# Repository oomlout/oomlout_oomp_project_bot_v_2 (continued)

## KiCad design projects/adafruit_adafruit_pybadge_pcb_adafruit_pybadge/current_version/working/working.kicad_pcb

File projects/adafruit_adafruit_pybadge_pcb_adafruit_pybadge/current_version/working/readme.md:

# adafruit_pybadge_pcb
 
## summary 
* id: adafruit_adafruit_pybadge_pcb_adafruit_pybadge
* user: adafruit
* name: adafruit_pybadge_pcb
* board: adafruit_pybadge
* repo: https://github.com/adafruit/Adafruit-PyBadge-PCB

* src_file_repo_sch: 
* src_file_repo_sch_link: https://github.com/adafruit/Adafruit-PyBadge-PCB/tree/master/
* full details link: https://github.com/oomlout/oomlout_oomp_project_bot_v_2/tree/main/projects/adafruit_adafruit_pybadge_pcb_adafruit_pybadge/current_version/working  

## schematic  
  
[schematic (pdf)](working_schematic.pdf) 

## pcb  

[board (pdf)](working.pdf)  

## working_bom
| Id | Designator | Footprint | Quantity | Designation | Supplier and ref |  | None | 
| --- | --- | --- | --- | --- | --- | --- | --- | 
| 1 | MS1 | FEATHERWING_SMT_NOHOLES | 1 | FEATHERWING_SMTDUALNOHOLES |  |  | [''] | 
| 2 | U4 | ALS-PT26-21C | 1 | ALS-PT21 |  |  | [''] | 
| 3 | C8,C6,C3 | 0805-NO | 3 | 10ÂµF |  |  | [''] | 
| 4 | SJ2 | SOLDERJUMPER_CLOSEDWIRE | 1 |  |  |  | [''] | 
| 5 | U$17,U$15,U$5,U$6 | MOUNTINGHOLE_3.0_PLATEDTHIN | 4 | MOUNTINGHOLE3.0THIN |  |  | [''] | 
| 6 | X1 | JSTPH2 | 1 | JSTPH |  |  | [''] | 
| 7 | C10,C5,C15,C14,C18,C11 | 0805-NO | 6 | 10uF |  |  | [''] | 
| 8 | X2 | 2X05_1.27MM_BOX_POSTS | 1 | 2x5 0.05 SWD" |  |  | [''] | 
| 9 | R14,R15,R3 | 0603-NO | 3 | 10K |  |  | [''] | 
| 10 | FB1 | 0805-NO | 1 | Ferrite |  |  | [''] | 
| 11 | Q1,Q2 | SOT23-R | 2 | DMG3405 |  |  | [''] | 
| 12 | D2,D1 | SOD-323 | 2 | 3.6V |  |  | [''] | 
| 13 | R1,R10,R11 | RESPACK_4X0603 | 3 | 100K |  |  | [''] | 
| 14 | R17,R19 | 0603-NO | 2 | 100K |  |  | [''] | 
| 15 | R7 | 0603-NO | 1 | 2.2K |  |  | [''] | 
| 16 | L0 | CHIPLED_0805_NOOUTLINE | 1 | RED |  |  | [''] | 
| 17 | NEOPIX0,SENSE0 | JSTPH3 | 2 | JST PH 3 |  |  | [''] | 
| 18 | C7,C1,C4,C12,C2,C13,C19 | 0603-NO | 7 | 1uF |  |  | [''] | 
| 19 | R8 | 0603-NO | 1 | 4.7K |  |  | [''] | 
| 20 | IC2 | SOT23-6 | 1 | PAM8301 |  |  | [''] | 
| 21 | U1 | SOIC8_208MIL | 1 | GD25Q16 |  |  | [''] | 
| 22 | SJ1 | SOLDERJUMPER_2WAY_OPEN_NOPASTE | 1 |  |  |  | [''] | 
| 23 | IC4 | LGA16_3X3MM | 1 | LIS3DH |  |  | [''] | 
| 24 | R16 | 0603-NO | 1 | 10 |  |  | [''] | 
| 25 | TP7,TP6,TP8 | TESTPOINT_ROUND_2MM | 3 |  |  |  | [''] | 
| 26 | C16 | _0805MP | 1 | 10ÂµF |  |  | [''] | 
| 27 | IC1 | TSSOP16 | 1 | 74165TSSOP |  |  | [''] | 
| 28 | C17,C9 | 0603-NO | 2 | 0.1uF |  |  | [''] | 
| 29 | U$13 | 53398-0271 | 1 | CON_MOLEX_2P |  |  | [''] | 
| 30 | Q4 | SOT363 | 1 | BSS138 |  |  | [''] | 
| 31 | R6,R5,R2 | 0603-NO | 3 | 1K |  |  | [''] | 
| 32 | U$8 | SPEAKER_OVAL8OHM | 1 |  |  |  | [''] | 
| 33 | U$34,U$35,U$42,U$43 | FIDUCIAL_1MM | 4 | FIDUCIAL_1MM |  |  | [''] | 
| 34 | D4 | SOD-123 | 1 | MBR0540 |  |  | [''] | 
| 35 | CHG0 | CHIPLED_0805_NOOUTLINE | 1 | ORANGE |  |  | [''] | 
| 36 | R12 | 0603-NO | 1 | 47K |  |  | [''] | 
| 37 | SW1 | EVQ-Q2_SMALLER | 1 | SPST_TACT-EVQQ2 |  |  | [''] | 
| 38 | U$32 | PYBADGE_BOT | 1 |  |  |  | [''] | 
| 39 | U$37 | PCBFEAT-REV-040 | 1 |  |  |  | [''] | 
| 40 | X3 | 4UCONN_20329_V2 | 1 | microUSB |  |  | [''] | 
| 41 | U2 | SOT23-5 | 1 | AP2112-3.3 |  |  | [''] | 
| 42 | SW11 | SPDT_SMT_SSSS811101 | 1 |  |  |  | [''] | 
| 43 | SP1 | BUZZER_SMT_7.5MM | 1 | SPEAKER_7.5MM |  |  | [''] | 
| 44 | U3 | SOT23-5 | 1 | MCP73831T-2ACI/OT |  |  | [''] | 
| 45 | I2C0 | JSTPH4 | 1 | JST PH 4 |  |  | [''] | 
| 46 | Q3 | SOT23-WIDE | 1 | BSS138 |  |  | [''] | 
| 47 | R4 | RESPACK_4X0603 | 1 | 10K |  |  | [''] | 
| 48 | U$24 | PQFN64-1 | 1 | ATSAMD51J19 |  |  | [''] | 
| 49 | LED3,LED4,LED1,LED5,LED2 | LED3535 | 5 | WS2812B3535 |  |  | [''] | 
| 50 | B0,RIGHT0,A0,LEFT0,START0,DOWN0,SELECT0,UP0 | 6MM_SMT | 8 |  |  |  | [''] | 
| 51 | U$18 | PYBADGE_TOP | 1 |  |  |  | [''] | 
| 52 | LCD1 | JD-T1800 | 1 | DISP_LCD_JDT1800 |  |  | [''] | 
| 53 | R9 | 0603-NO | 1 | DNP |  |  | [''] | 

## bom_schematic
| Ref | Qnty | Value | Cmp name | Footprint | Description | Vendor | DNP | 
| --- | --- | --- | --- | --- | --- | --- | --- | 
| A0 | 1 | SWITCH_TACT_SMT_6MMSMALL | SWITCH_TACT_SMT_6MMSMALL | working:6MM_SMT |  |  |  | 
| B0 | 1 | SWITCH_TACT_SMT_6MMSMALL | SWITCH_TACT_SMT_6MMSMALL | working:6MM_SMT |  |  |  | 
| C1, C2, C4, C7, C12, C13, C19 | 7 | 1uF | CAP_CERAMIC0603_NO | working:0603-NO |  |  |  | 
| C3, C6, C8 | 3 | 10ÂµF | CAP_CERAMIC0805-NOOUTLINE | working:0805-NO |  |  |  | 
| C5, C10, C11, C14, C15, C18 | 6 | 10uF | CAP_CERAMIC0805-NOOUTLINE | working:0805-NO |  |  |  | 
| C9, C17 | 2 | 0.1uF | CAP_CERAMIC0603_NO | working:0603-NO |  |  |  | 
| C16 | 1 | 10ÂµF | CAP_CERAMIC_0805MP | working:_0805MP |  |  |  | 
| CHG0 | 1 | ORANGE | LED0805_NOOUTLINE | working:CHIPLED_0805_NOOUTLINE |  |  |  | 
| D1, D2 | 2 | 3.6V | DIODE-ZENERSOD323 | working:SOD-323 |  |  |  | 
| D4 | 1 | MBR0540 | DIODE-SCHOTTKYSOD-123 | working:SOD-123 |  |  |  | 
| DOWN0 | 1 | SWITCH_TACT_SMT_6MMSMALL | SWITCH_TACT_SMT_6MMSMALL | working:6MM_SMT |  |  |  | 
| FB1 | 1 | Ferrite | FERRITE-0805NO | working:0805-NO |  |  |  | 
| I2C0 | 1 | STEMMA_I2C_RASMT | STEMMA_I2C_RASMT | working:JSTPH4 |  |  |  | 
| IC1 | 1 | 74165TSSOP | 74165TSSOP | working:TSSOP16 |  |  |  | 
| IC2 | 1 | PAM8301 | PAM8301 | working:SOT23-6 |  |  |  | 
| IC4 | 1 | LIS3DH | ACCEL_LIS3DHTR | working:LGA16_3X3MM |  |  |  | 
| L0 | 1 | RED | LED0805_NOOUTLINE | working:CHIPLED_0805_NOOUTLINE |  |  |  | 
| LCD1 | 1 | DISP_LCD_JDT1800 | DISP_LCD_JDT1800 | working:JD-T1800 |  |  |  | 
| LED1, LED2, LED3, LED4, LED5 | 5 | WS2812B3535 | WS2812B3535 | working:LED3535 |  |  |  | 
| LEFT0 | 1 | SWITCH_TACT_SMT_6MMSMALL | SWITCH_TACT_SMT_6MMSMALL | working:6MM_SMT |  |  |  | 
| MS1 | 1 | FEATHERWING_SMTDUALNOHOLES | FEATHERWING_SMTDUALNOHOLES | working:FEATHERWING_SMT_NOHOLES |  |  |  | 
| NEOPIX0 | 1 | JST PH 3 | CON_JST_PH_3PIN | working:JSTPH3 |  |  |  | 
| Q1, Q2 | 2 | DMG3405 | MOSFET-P | working:SOT23-R |  |  |  | 
| Q3 | 1 | BSS138 | MOSFET-NWIDE | working:SOT23-WIDE |  |  |  | 
| Q4 | 1 | BSS138 | MOSFET-N_DUAL | working:SOT363 |  |  |  | 
| R1, R10, R11 | 3 | 100K | RESISTOR_4PACK | working:RESPACK_4X0603 |  |  |  | 
| R2, R5, R6 | 3 | 1K | RESISTOR_0603_NOOUT | working:0603-NO |  |  |  | 
| R3, R14, R15 | 3 | 10K | RESISTOR_0603_NOOUT | working:0603-NO |  |  |  | 
| R4 | 1 | 10K | RESISTOR_4PACK | working:RESPACK_4X0603 |  |  |  | 
| R7 | 1 | 2.2K | RESISTOR_0603_NOOUT | working:0603-NO |  |  |  | 
| R8 | 1 | 4.7K | RESISTOR_0603_NOOUT | working:0603-NO |  |  |  | 
| R9 | 1 | DNP | RESISTOR_0603_NOOUT | working:0603-NO |  |  |  | 
| R12 | 1 | 47K | RESISTOR_0603_NOOUT | working:0603-NO |  |  |  | 
| R16 | 1 | 10 | RESISTOR_0603_NOOUT | working:0603-NO |  |  |  | 
| R17, R19 | 2 | 100K | RESISTOR_0603_NOOUT | working:0603-NO |  |  |  | 
| RIGHT0 | 1 | SWITCH_TACT_SMT_6MMSMALL | SWITCH_TACT_SMT_6MMSMALL | working:6MM_SMT |  |  |  | 
| SELECT0 | 1 | SWITCH_TACT_SMT_6MMSMALL | SWITCH_TACT_SMT_6MMSMALL | working:6MM_SMT |  |  |  | 
| SENSE0 | 1 | JST PH 3 | CON_JST_PH_3PIN | working:JSTPH3 |  |  |  | 
| SJ1 | 1 | SOLDERJUMPER_2WAY | SOLDERJUMPER_2WAY | working:SOLDERJUMPER_2WAY_OPEN_NOPASTE |  |  |  | 
| SJ2 | 1 | SOLDERJUMPERCLOSED | SOLDERJUMPERCLOSED | working:SOLDERJUMPER_CLOSEDWIRE |  |  |  | 
| SP1 | 1 | SPEAKER_7.5MM | SPEAKER_7.5MM | working:BUZZER_SMT_7.5MM |  |  |  | 
| START0 | 1 | SWITCH_TACT_SMT_6MMSMALL | SWITCH_TACT_SMT_6MMSMALL | working:6MM_SMT |  |  |  | 
| SW1 | 1 | SPST_TACT-EVQQ2 | SWITCH_TACT_SMT_EVQQ2_SMALL | working:EVQ-Q2_SMALLER |  |  |  | 
| SW11 | 1 | SWITCH_SPDT | SWITCH_SPDT | working:SPDT_SMT_SSSS811101 |  |  |  | 
| TP6, TP7, TP8 | 3 | TESTPOINTROUND2MM | TESTPOINTROUND2MM | working:TESTPOINT_ROUND_2MM |  |  |  | 
| U1 | 1 | GD25Q16 | SPIFLASH_8PIN208MIL | working:SOIC8_208MIL |  |  |  | 
| U2 | 1 | AP2112-3.3 | VREG_SOT23-5 | working:SOT23-5 |  |  |  | 
| U3 | 1 | MCP73831T-2ACI/OT | MCP73831/2 | working:SOT23-5 |  |  |  | 
| U4 | 1 | ALS-PT21 | PHOTOTRANSISTOR_PT26-21C | working:ALS-PT26-21C |  |  |  | 
| U$5, U$6, U$15, U$17 | 4 | MOUNTINGHOLE3.0THIN | MOUNTINGHOLE3.0THIN | working:MOUNTINGHOLE_3.0_PLATEDTHIN |  |  |  | 
| U$13 | 1 | CON_MOLEX_2P | CON_MOLEX_2P | working:53398-0271 |  |  |  | 
| U$24 | 1 | ATSAMD51J | ATSAMD51J | working:PQFN64-1 |  |  |  | 
| U$34, U$35, U$42, U$43 | 4 | FIDUCIAL_1MM | FIDUCIAL_1MM | working:FIDUCIAL_1MM |  |  |  | 
| UP0 | 1 | SWITCH_TACT_SMT_6MMSMALL | SWITCH_TACT_SMT_6MMSMALL | working:6MM_SMT |  |  |  | 
| X1 | 1 | JSTPH | CON_JST_PH_2PIN | working:JSTPH2 |  |  |  | 
| X2 | 1 | 2x5 0.05" SWD | JTAG-CORTEXBOXPOSTS | working:2X05_1.27MM_BOX_POSTS |  |  |  | 
| X3 | 1 | microUSB | USB_MICRO_20329_V2 | working:4UCONN_20329_V2 |  |  |  | 

## mounting_holes
| x | y | package | value | ref | size | 
| --- | --- | --- | --- | --- | --- | 
| 0.0 | 46.36 | MOUNTINGHOLE_3.0_PLATEDTHIN | MOUNTINGHOLE3.0THIN | U$5 | m3 | 
| 78.1 | 46.36 | MOUNTINGHOLE_3.0_PLATEDTHIN | MOUNTINGHOLE3.0THIN | U$6 | m3 | 
| 0.0 | 0.0 | MOUNTINGHOLE_3.0_PLATEDTHIN | MOUNTINGHOLE3.0THIN | U$15 | m3 | 
| 78.1 | 0.0 | MOUNTINGHOLE_3.0_PLATEDTHIN | MOUNTINGHOLE3.0THIN | U$17 | m3 |

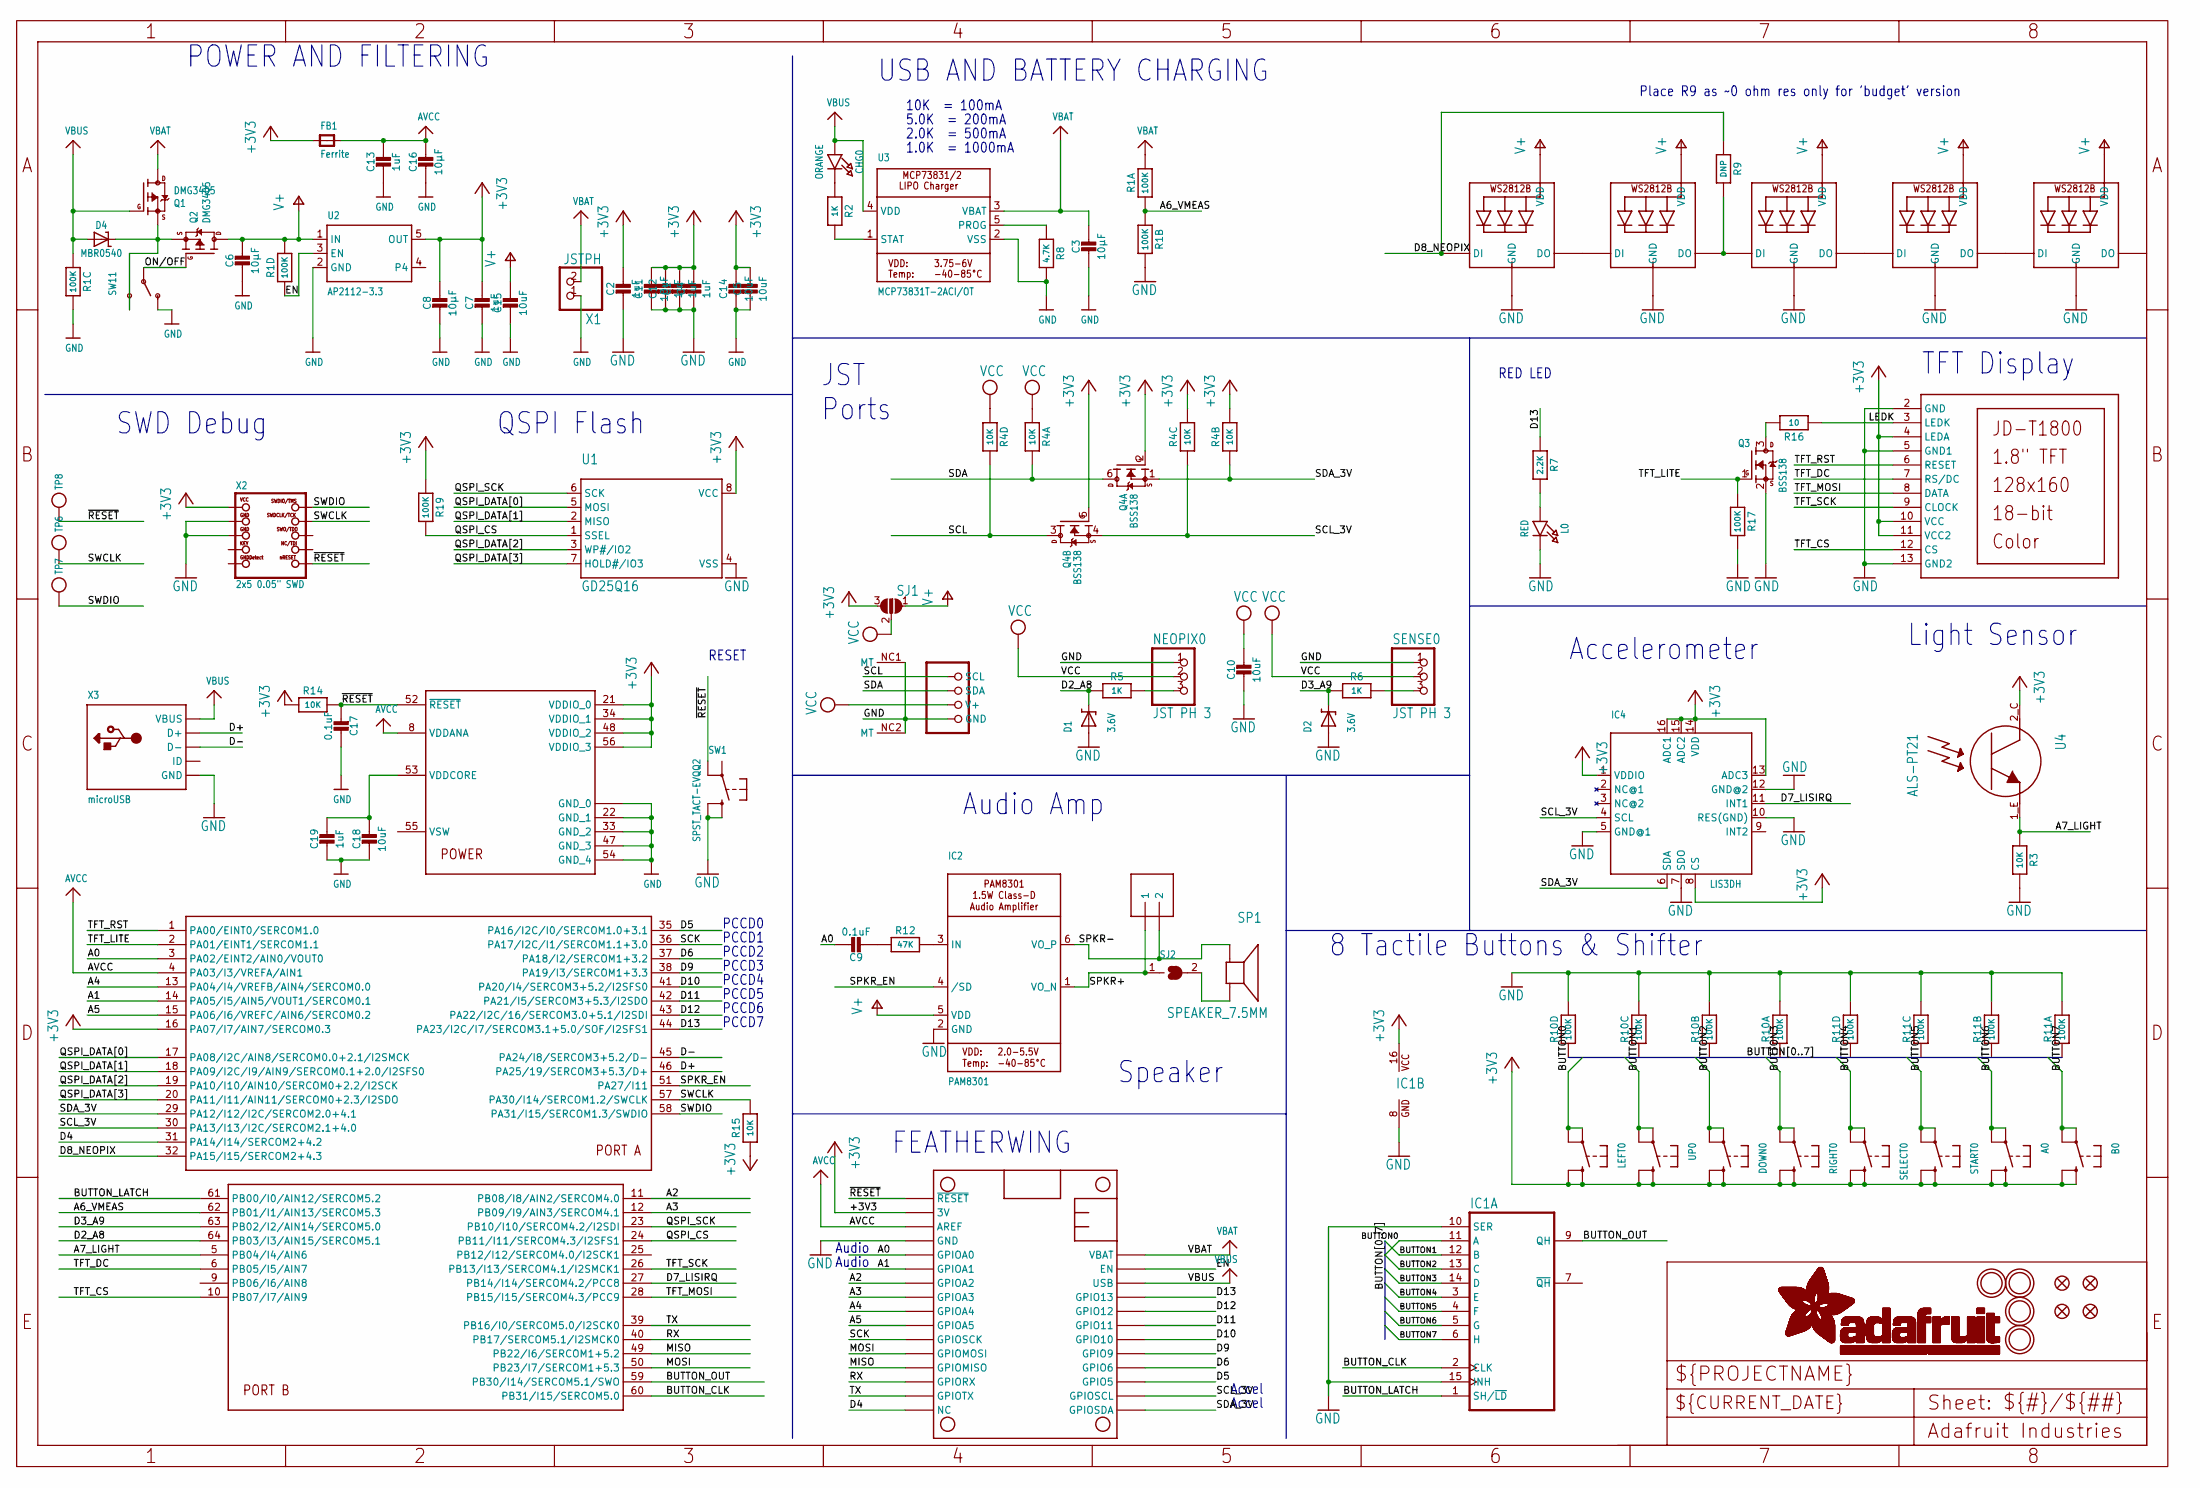
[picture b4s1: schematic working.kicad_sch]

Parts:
A0: SWITCH_TACT_SMT_6MMSMALL; 6MM_SMT
B0: SWITCH_TACT_SMT_6MMSMALL; 6MM_SMT
C1, C2, C4, C7, C12, C13, C19: 1uF; 0603-NO
C3, C6, C8: 10µF; 0805-NO
C5, C10, C11, C14, C15, C18: 10uF; 0805-NO
C9, C17: 0.1uF; 0603-NO
C16: 10µF; _0805MP
CHG0: ORANGE; CHIPLED_0805_NOOUTLINE
D1, D2: 3.6V; SOD-323
D4: MBR0540; SOD-123
DOWN0: SWITCH_TACT_SMT_6MMSMALL; 6MM_SMT
FB1: Ferrite; 0805-NO
I2C0: STEMMA_I2C_RASMT; JSTPH4
IC1: 74165TSSOP; TSSOP16
IC2: PAM8301; SOT23-6
IC4: LIS3DH; LGA16_3X3MM
L0: RED; CHIPLED_0805_NOOUTLINE
LCD1: DISP_LCD_JDT1800; JD-T1800
LED1, LED2, LED3, LED4, LED5: WS2812B3535; LED3535
LEFT0: SWITCH_TACT_SMT_6MMSMALL; 6MM_SMT
MS1: FEATHERWING_SMTDUALNOHOLES; FEATHERWING_SMT_NOHOLES
NEOPIX0: JST PH 3; JSTPH3
Q1, Q2: DMG3405; SOT23-R
Q3: BSS138; SOT23-WIDE
Q4: BSS138; SOT363
R1, R10, R11: 100K; RESPACK_4X0603
R2, R5, R6: 1K; 0603-NO
R3, R14, R15: 10K; 0603-NO
R4: 10K; RESPACK_4X0603
R7: 2.2K; 0603-NO
R8: 4.7K; 0603-NO
R9: DNP; 0603-NO
R12: 47K; 0603-NO
R16: 10; 0603-NO
R17, R19: 100K; 0603-NO
RIGHT0: SWITCH_TACT_SMT_6MMSMALL; 6MM_SMT
SELECT0: SWITCH_TACT_SMT_6MMSMALL; 6MM_SMT
SENSE0: JST PH 3; JSTPH3
SJ1: SOLDERJUMPER_2WAY; SOLDERJUMPER_2WAY_OPEN_NOPASTE
SJ2: SOLDERJUMPERCLOSED; SOLDERJUMPER_CLOSEDWIRE
SP1: SPEAKER_7.5MM; BUZZER_SMT_7.5MM
START0: SWITCH_TACT_SMT_6MMSMALL; 6MM_SMT
SW1: SPST_TACT-EVQQ2; EVQ-Q2_SMALLER
SW11: SWITCH_SPDT; SPDT_SMT_SSSS811101
TP6, TP7, TP8: TESTPOINTROUND2MM; TESTPOINT_ROUND_2MM
U1: GD25Q16; SOIC8_208MIL
U2: AP2112-3.3; SOT23-5
U3: MCP73831T-2ACI/OT; SOT23-5
U4: ALS-PT21; ALS-PT26-21C
U$5, U$6, U$15, U$17: MOUNTINGHOLE3.0THIN; MOUNTINGHOLE_3.0_PLATEDTHIN
U$13: CON_MOLEX_2P; 53398-0271
U$24: ATSAMD51J; PQFN64-1
U$34, U$35, U$42, U$43: FIDUCIAL_1MM
UP0: SWITCH_TACT_SMT_6MMSMALL; 6MM_SMT
X1: JSTPH; JSTPH2
X2: 2x5 0.05" SWD; 2X05_1.27MM_BOX_POSTS
X3: microUSB; 4UCONN_20329_V2

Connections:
+3V3: A0.B (S), A0.B' (S1), B0.B (S), B0.B' (S1), C1.1, C2.1, C4.1, C5.1, C7.1, C8.1, C11.1, C12.1, C14.1, DOWN0.B (S), DOWN0.B' (S1), FB1.1, IC1.16 (VCC), IC4.1 (VDDIO), IC4.8 (CS), IC4.13 (ADC3), IC4.14 (VDD), IC4.15 (ADC2), IC4.16 (ADC1), LCD1.4 (LEDA), LCD1.10 (VCC), LCD1.11 (VCC2), LEFT0.B (S), LEFT0.B' (S1), MS1.2 (3V), MS1.2B (3V), Q4.2 (G), Q4.5 (G), R4.2 (1), R4.3 (1), R14.1, R15.1, R19.1, RIGHT0.B (S), RIGHT0.B' (S1), SELECT0.B (S), SELECT0.B' (S1), SJ1.3, START0.B (S), START0.B' (S1), U1.8 (VCC), U2.5 (OUT), U4.2_C (C), U$24.16 (PA07/I7/AIN7/SERCOM0.3), U$24.21 (VDDIO_0), U$24.34 (VDDIO_1), U$24.48 (VDDIO_2), U$24.56 (VDDIO_3), UP0.B (S), UP0.B' (S1), X2.1 (VCC)
A0: C9.1, MS1.5 (GPIOA0), MS1.5B (GPIOA0), U$24.3 (PA02/EINT2/AIN0/VOUT0)
A1: MS1.6 (GPIOA1), MS1.6B (GPIOA1), U$24.14 (PA05/I5/AIN5/VOUT1/SERCOM0.1)
A2: MS1.7 (GPIOA2), MS1.7B (GPIOA2), U$24.11 (PB08/I8/AIN2/SERCOM4.0)
A3: MS1.8 (GPIOA3), MS1.8B (GPIOA3), U$24.12 (PB09/I9/AIN3/SERCOM4.1)
A4: MS1.9 (GPIOA4), MS1.9B (GPIOA4), U$24.13 (PA04/I4/VREFB/AIN4/SERCOM0.0)
A5: MS1.10 (GPIOA5), MS1.10B (GPIOA5), U$24.15 (PA06/I6/VREFC/AIN6/SERCOM0.2)
A6_VMEAS: R1.1, R1.2 (1), U$24.62 (PB01/I1/AIN13/SERCOM5.3)
A7_LIGHT: R3.2, U4.1_E (E), U$24.5 (PB04/I4/AIN6)
AVCC: C13.1, C16.1, FB1.2, MS1.3 (AREF), MS1.3B (AREF), U$24.4 (PA03/I3/VREFA/AIN1), U$24.8 (VDDANA)
BUTTON0: IC1.11 (A), LEFT0.A, LEFT0.A' (P1), R10.4 (1)
BUTTON1: IC1.12 (B), R10.3 (1), UP0.A, UP0.A' (P1)
BUTTON2: DOWN0.A, DOWN0.A' (P1), IC1.13 (C), R10.2 (1)
BUTTON3: IC1.14 (D), R10.1, RIGHT0.A, RIGHT0.A' (P1)
BUTTON4: IC1.3 (E), R11.4 (1), SELECT0.A, SELECT0.A' (P1)
BUTTON5: IC1.4 (F), R11.3 (1), START0.A, START0.A' (P1)
BUTTON6: A0.A, A0.A' (P1), IC1.5 (G), R11.2 (1)
BUTTON7: B0.A, B0.A' (P1), IC1.6 (H), R11.1
BUTTON_CLK: IC1.2 (CLK), U$24.60 (PB31/I15/SERCOM5.0)
BUTTON_LATCH: IC1.1 (SH/~LD), U$24.61 (PB00/I0/AIN12/SERCOM5.2)
BUTTON_OUT: IC1.9 (QH), U$24.59 (PB30/I14/SERCOM5.1/SWO)
CHG_LED: R2.2, U3.1 (STAT)
CHG_RATE: R8.1, U3.5 (PROG)
D2_: NEOPIX0.3, R5.1
D2_A8: D1.C, R5.2, U$24.64 (PB03/I3/AIN15/SERCOM5.1)
D3_: R6.1, SENSE0.3
D3_A9: D2.C, R6.2, U$24.63 (PB02/I2/AIN14/SERCOM5.0)
D4: MS1.16 (NC), MS1.16B (NC), U$24.31 (PA14/I14/SERCOM2+4.2)
D5: MS1.19 (GPIO5), MS1.19B (GPIO5), U$24.35 (PA16/I2C/I0/SERCOM1.0+3.1)
D6: MS1.20 (GPIO6), MS1.20B (GPIO6), U$24.37 (PA18/I2/SERCOM1+3.2)
D7_LISIRQ: IC4.11 (INT1), U$24.27 (PB14/I14/SERCOM4.2/PCC8)
D8_NEOPIX: LED1.1 (DI), R9.1, U$24.32 (PA15/I15/SERCOM2+4.3)
D9: MS1.21 (GPIO9), MS1.21B (GPIO9), U$24.38 (PA19/I3/SERCOM1+3.3)
D10: MS1.22 (GPIO10), MS1.22B (GPIO10), U$24.41 (PA20/I4/SERCOM3+5.2/I2SFS0)
D11: MS1.23 (GPIO11), MS1.23B (GPIO11), U$24.42 (PA21/I5/SERCOM3+5.3/I2SDO)
D12: MS1.24 (GPIO12), MS1.24B (GPIO12), U$24.43 (PA22/I2C/16/SERCOM3.0+5.1/I2SDI)
D13: MS1.25 (GPIO13), MS1.25B (GPIO13), R7.1, U$24.44 (PA23/I2C/I7/SERCOM3.1+5.0/SOF/I2SFS1)
D+: U$24.46 (PA25/19/SERCOM3+5.3/D+), X3.D+
D-: U$24.45 (PA24/I8/SERCOM3+5.2/D-), X3.D-
EN: MS1.27 (EN), MS1.27B (EN), R1.4 (1), U2.3 (EN)
GND: C1.2, C2.2, C3.2, C4.2, C5.2, C6.2, C7.2, C8.2, C10.2, C11.2, C12.2, C13.2, C14.2, C15.2, C16.2, C17.1, C18.2, C19.2, D1.A, D2.A, I2C0.1 (GND), I2C0.NC1 (MT), I2C0.NC2 (MT), IC1.8 (GND), IC1.10 (SER), IC1.15 (INH), IC2.2 (GND), IC4.5 (GND@1), IC4.7 (SDO), IC4.10 (RES(GND)), IC4.12 (GND@2), L0.C, LCD1.2 (GND), LCD1.5 (GND1), LCD1.13 (GND2), LED1.4 (GND), LED2.4 (GND), LED3.4 (GND), LED4.4 (GND), LED5.4 (GND), MS1.4 (GND), MS1.4B (GND), NEOPIX0.1, Q3.2 (S), R1.6 (2), R1.7 (2), R3.1, R8.2, R10.5 (2), R10.6 (2), R10.7 (2), R10.8 (2), R11.5 (2), R11.6 (2), R11.7 (2), R11.8 (2), R17.2, SENSE0.1, SW1.B (S), SW1.B' (S1), SW11.A (O), U1.4 (VSS), U2.2 (GND), U3.2 (VSS), U$24.7 (GND_0), U$24.22 (GND_1), U$24.33 (GND_2), U$24.47 (GND_3), U$24.54 (GND_4), U$24.EXP (GND_0), X1.1, X2.3 (GND@1), X2.5 (GND@2), X3.BASE@1 (GND), X3.BASE@2 (GND), X3.GND, X3.SPRT@1 (GND), X3.SPRT@2 (GND), X3.SPRT@3 (GND), X3.SPRT@4 (GND)
LEDK: LCD1.3 (LEDK), R16.1
MISO: MS1.13 (GPIOMISO), MS1.13B (GPIOMISO), U$24.49 (PB22/I6/SERCOM1+5.2)
MOSI: MS1.12 (GPIOMOSI), MS1.12B (GPIOMOSI), U$24.50 (PB23/I7/SERCOM1+5.3)
unnamed: CHG0.C, R2.1
unnamed: L0.A, R7.2
unnamed: LED1.3 (DO), LED2.1 (DI)
unnamed: LED2.3 (DO), LED3.1 (DI), R9.2
unnamed: LED3.3 (DO), LED4.1 (DI)
unnamed: Q3.3 (D), R16.2
unnamed: LED4.3 (DO), LED5.1 (DI)
unnamed: D4.C, Q1.2 (S), Q2.2 (S), SW11.C (S)
unnamed: C9.2, R12.1
unnamed: IC2.3 (IN), R12.2
unnamed: SJ2.2, SP1.-
ON/OFF: Q2.1 (G), SW11.B
QSPI_CS: R19.2, U1.1 (SSEL), U$24.24 (PB11/I11/SERCOM4.3/I2SFS1)
QSPI_DATA[0]: U1.5 (MOSI), U$24.17 (PA08/I2C/AIN8/SERCOM0.0+2.1/I2SMCK)
QSPI_DATA[1]: U1.2 (MISO), U$24.18 (PA09/I2C/I9/AIN9/SERCOM0.1+2.0/I2SFS0)
QSPI_DATA[2]: U1.3 (WP#/IO2), U$24.19 (PA10/I10/AIN10/SERCOM0+2.2/I2SCK)
QSPI_DATA[3]: U1.7 (HOLD#/IO3), U$24.20 (PA11/I11/AIN11/SERCOM0+2.3/I2SDO)
QSPI_SCK: U1.6 (SCK), U$24.23 (PB10/I10/SERCOM4.2/I2SDI)
RX: MS1.14 (GPIORX), MS1.14B (GPIORX), U$24.40 (PB17/SERCOM5.1/I2SMCK0)
SCK: MS1.11 (GPIOSCK), MS1.11B (GPIOSCK), U$24.36 (PA17/I2C/I1/SERCOM1.1+3.0)
SCL: I2C0.4 (SCL), Q4.3 (D), R4.5 (2)
SCL_3V: IC4.4 (SCL), MS1.18 (GPIOSCL), MS1.18B (GPIOSCL), Q4.4 (S), R4.6 (2), U$24.30 (PA13/I13/I2C/SERCOM2.1+4.0)
SDA: I2C0.3 (SDA), Q4.6 (D), R4.8 (2)
SDA_3V: IC4.6 (SDA), MS1.17 (GPIOSDA), MS1.17B (GPIOSDA), Q4.1 (S), R4.7 (2), U$24.29 (PA12/I12/I2C/SERCOM2.0+4.1)
SPKR+: IC2.1 (VO_N), SJ2.1, U$13.1
SPKR-: IC2.6 (VO_P), SP1.+, U$13.2
SPKR_EN: IC2.4 (/SD), U$24.51 (PA27/I11)
SWCLK: R15.2, TP6.P$1, U$24.57 (PA30/I14/SERCOM1.2/SWCLK), X2.4 (SWDCLK)
SWDIO: TP7.P$1, U$24.58 (PA31/I15/SERCOM1.3/SWDIO), X2.2 (SWDIO)
TFT_CS: LCD1.12 (CS), U$24.10 (PB07/I7/AIN9)
TFT_DC: LCD1.7 (RS/DC), U$24.6 (PB05/I5/AIN7)
TFT_LITE: Q3.1 (G), R17.1, U$24.2 (PA01/EINT1/SERCOM1.1)
TFT_MOSI: LCD1.8 (DATA), U$24.28 (PB15/I15/SERCOM4.3/PCC9)
TFT_RST: LCD1.6 (RESET), U$24.1 (PA00/EINT0/SERCOM1.0)
TFT_SCK: LCD1.9 (CLOCK), U$24.26 (PB13/I13/SERCOM4.1/I2SMCK1)
TX: MS1.15 (GPIOTX), MS1.15B (GPIOTX), U$24.39 (PB16/I0/SERCOM5.0/I2SCK0)
V+: C6.1, C15.1, IC2.5 (VDD), LED1.2 (VDD), LED2.2 (VDD), LED3.2 (VDD), LED4.2 (VDD), LED5.2 (VDD), Q2.3 (D), R1.5 (2), SJ1.1, U2.1 (IN)
VBAT: C3.1, MS1.28 (VBAT), MS1.28B (VBAT), Q1.3 (D), R1.8 (2), U3.3 (VBAT), X1.2
VBUS: CHG0.A, D4.A, MS1.26 (USB), MS1.26B (USB), Q1.1 (G), R1.3 (1), U3.4 (VDD), X3.VBUS
VCC: C10.1, I2C0.2 (V+), NEOPIX0.2, R4.1, R4.4 (1), SENSE0.2, SJ1.2
VDDCORE2: C18.1, C19.1, U$24.53 (VDDCORE)
~RESET: C17.2, MS1.1 (~RESET), MS1.1B (~RESET), R14.2, SW1.A' (P1), TP8.P$1, U$24.52 (~RESET), X2.10 (NRESET)

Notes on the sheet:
SWD Debug
5.0K = 200mA
FEATHERWING
10K = 100mA
1.0K = 1000mA
JST Ports
PCCD0
8 Tactile Buttons & Shifter
Audio Amp
PCCD3
POWER AND FILTERING
USB AND BATTERY CHARGING
TFT Display
Light Sensor
Audio
Place R9 as ~0 ohm res only for 'budget' version
RESET
PCCD6
PCCD5
PCCD2
RED LED
PCCD1
PCCD7
Accel
QSPI Flash
Speaker
2.0K = 500mA
Accelerometer
PCCD4

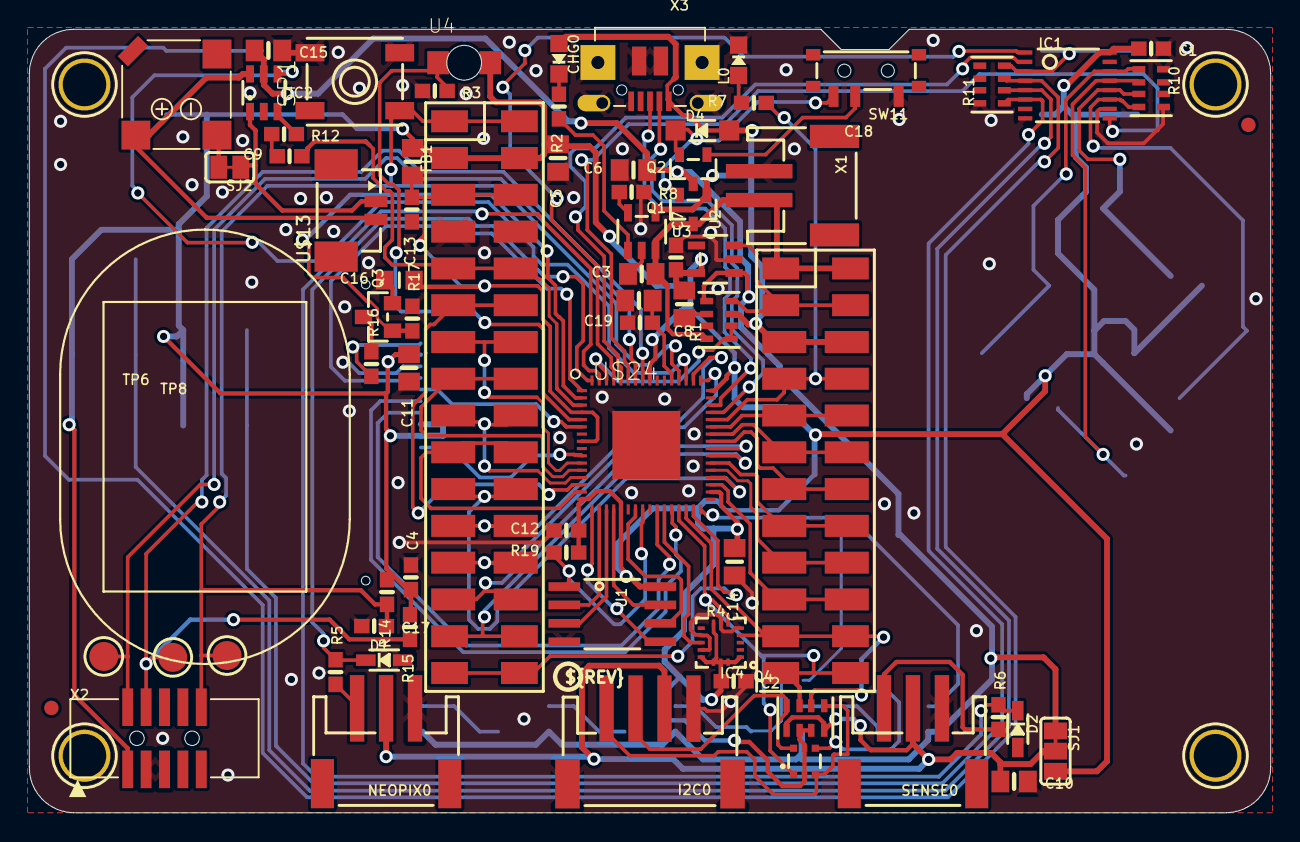
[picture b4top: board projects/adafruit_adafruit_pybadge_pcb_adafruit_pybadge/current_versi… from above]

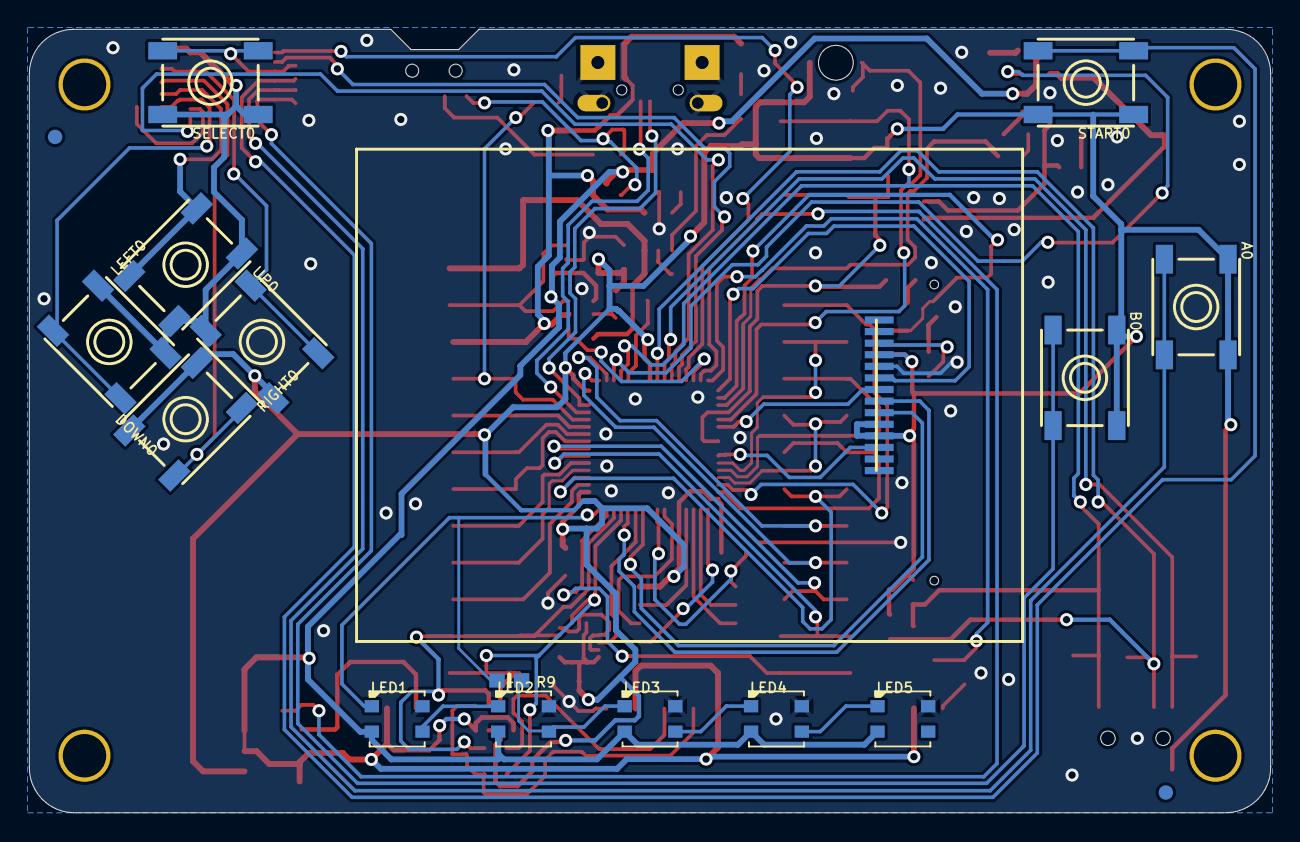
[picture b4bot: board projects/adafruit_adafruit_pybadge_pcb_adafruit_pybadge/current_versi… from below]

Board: 2 copper layers, 85.7 x 54.1 mm, 96 parts (18 on the bottom side), 86 nets.

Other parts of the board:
U$8: SPEAKER_OVAL8OHM
U$18: PYBADGE_TOP
U$32: PYBADGE_BOT
U$37: PCBFEAT-REV-040

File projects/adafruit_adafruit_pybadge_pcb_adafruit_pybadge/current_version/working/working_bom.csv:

"Id";"Designator";"Footprint";"Quantity";"Designation";"Supplier and ref";
1;"MS1";"FEATHERWING_SMT_NOHOLES";1;"FEATHERWING_SMTDUALNOHOLES";;;
2;"U4";"ALS-PT26-21C";1;"ALS-PT21";;;
3;"C8,C6,C3";"0805-NO";3;"10µF";;;
4;"SJ2";"SOLDERJUMPER_CLOSEDWIRE";1;"";;;
5;"U$17,U$15,U$5,U$6";"MOUNTINGHOLE_3.0_PLATEDTHIN";4;"MOUNTINGHOLE3.0THIN";;;
6;"X1";"JSTPH2";1;"JSTPH";;;
7;"C10,C5,C15,C14,C18,C11";"0805-NO";6;"10uF";;;
8;"X2";"2X05_1.27MM_BOX_POSTS";1;"2x5 0.05" SWD";;;
9;"R14,R15,R3";"0603-NO";3;"10K";;;
10;"FB1";"0805-NO";1;"Ferrite";;;
11;"Q1,Q2";"SOT23-R";2;"DMG3405";;;
12;"D2,D1";"SOD-323";2;"3.6V";;;
13;"R1,R10,R11";"RESPACK_4X0603";3;"100K";;;
14;"R17,R19";"0603-NO";2;"100K";;;
15;"R7";"0603-NO";1;"2.2K";;;
16;"L0";"CHIPLED_0805_NOOUTLINE";1;"RED";;;
17;"NEOPIX0,SENSE0";"JSTPH3";2;"JST PH 3";;;
18;"C7,C1,C4,C12,C2,C13,C19";"0603-NO";7;"1uF";;;
19;"R8";"0603-NO";1;"4.7K";;;
20;"IC2";"SOT23-6";1;"PAM8301";;;
21;"U1";"SOIC8_208MIL";1;"GD25Q16";;;
22;"SJ1";"SOLDERJUMPER_2WAY_OPEN_NOPASTE";1;"";;;
23;"IC4";"LGA16_3X3MM";1;"LIS3DH";;;
24;"R16";"0603-NO";1;"10";;;
25;"TP7,TP6,TP8";"TESTPOINT_ROUND_2MM";3;"";;;
26;"C16";"_0805MP";1;"10µF";;;
27;"IC1";"TSSOP16";1;"74165TSSOP";;;
28;"C17,C9";"0603-NO";2;"0.1uF";;;
29;"U$13";"53398-0271";1;"CON_MOLEX_2P";;;
30;"Q4";"SOT363";1;"BSS138";;;
31;"R6,R5,R2";"0603-NO";3;"1K";;;
32;"U$8";"SPEAKER_OVAL8OHM";1;"";;;
33;"U$34,U$35,U$42,U$43";"FIDUCIAL_1MM";4;"FIDUCIAL_1MM";;;
34;"D4";"SOD-123";1;"MBR0540";;;
35;"CHG0";"CHIPLED_0805_NOOUTLINE";1;"ORANGE";;;
36;"R12";"0603-NO";1;"47K";;;
37;"SW1";"EVQ-Q2_SMALLER";1;"SPST_TACT-EVQQ2";;;
38;"U$32";"PYBADGE_BOT";1;"";;;
39;"U$37";"PCBFEAT-REV-040";1;"";;;
40;"X3";"4UCONN_20329_V2";1;"microUSB";;;
41;"U2";"SOT23-5";1;"AP2112-3.3";;;
42;"SW11";"SPDT_SMT_SSSS811101";1;"";;;
43;"SP1";"BUZZER_SMT_7.5MM";1;"SPEAKER_7.5MM";;;
44;"U3";"SOT23-5";1;"MCP73831T-2ACI/OT";;;
45;"I2C0";"JSTPH4";1;"JST PH 4";;;
46;"Q3";"SOT23-WIDE";1;"BSS138";;;
47;"R4";"RESPACK_4X0603";1;"10K";;;
48;"U$24";"PQFN64-1";1;"ATSAMD51J19";;;
49;"LED3,LED4,LED1,LED5,LED2";"LED3535";5;"WS2812B3535";;;
50;"B0,RIGHT0,A0,LEFT0,START0,DOWN0,SELECT0,UP0";"6MM_SMT";8;"";;;
51;"U$18";"PYBADGE_TOP";1;"";;;
52;"LCD1";"JD-T1800";1;"DISP_LCD_JDT1800";;;
53;"R9";"0603-NO";1;"DNP";;;
